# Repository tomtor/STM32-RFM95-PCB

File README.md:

# AVR128DB28
AVR Printed Circuit Board for creating IOT nodes with the RFM95 LORA chip.

See:
- https://www.thethingsnetwork.org/forum/t/avr128db28-pcb-with-rfm95/50864
- https://www.thethingsnetwork.org/labs/story/a-cheap-stm32-arduino-node

for background and old software samples.

This repository now has tested LMIC (https://github.com/tomtor/STM32-RFM95-PCB/tree/master/AVR128DBLora) and RadioLib (https://github.com/tomtor/STM32-RFM95-PCB/tree/master/AVR128_RadioLib) Arduino code for the AVR128DB board with the RFM95W.

Schema: https://github.com/tomtor/STM32-RFM95-PCB/raw/master/AVR-LORA.pdf

Note that most components are optional:

- A LED to flash
- I2C 4K7 pull up resistors
- A lot of capacitors (mounting a single 1uF will do in most situations)
- 32.768kHz crystal
- 24MHz crystal
- MCP1700 regulator with 1uA idle current
- Schottky diode for charging NiMH batteries from a solar panel
- Voltage divider for measuring battery voltage

Aisler link for producing 1206 board: https://aisler.net/p/EAZHDDHF

Aisler link for producing 0805 board: https://aisler.net/p/ZRKAROVP

# STM32-RFM95-PCB
STM32 Printed Circuit Board for creating IOT nodes with the RFM95 LORA chip

See:
- https://www.thethingsnetwork.org/labs/story/a-cheap-stm32-arduino-node
- https://gist.github.com/tomtor/c754355f1b98370e78b4025f236d990e (Arduino sketch)

You can order this board here:

https://aisler.net/p/CZGCIFFH

Credits:

https://github.com/myelin/myelin-kicad-libraries (STM32 module KiCad library)

https://github.com/mysensors-kicad/mysensors_symbols (RFM95 KiCad library)

https://github.com/novirium/ESPilot/blob/master/lib/ESPilot.pretty/RFM95.kicad_mod (RFM95 KiCad footprint)

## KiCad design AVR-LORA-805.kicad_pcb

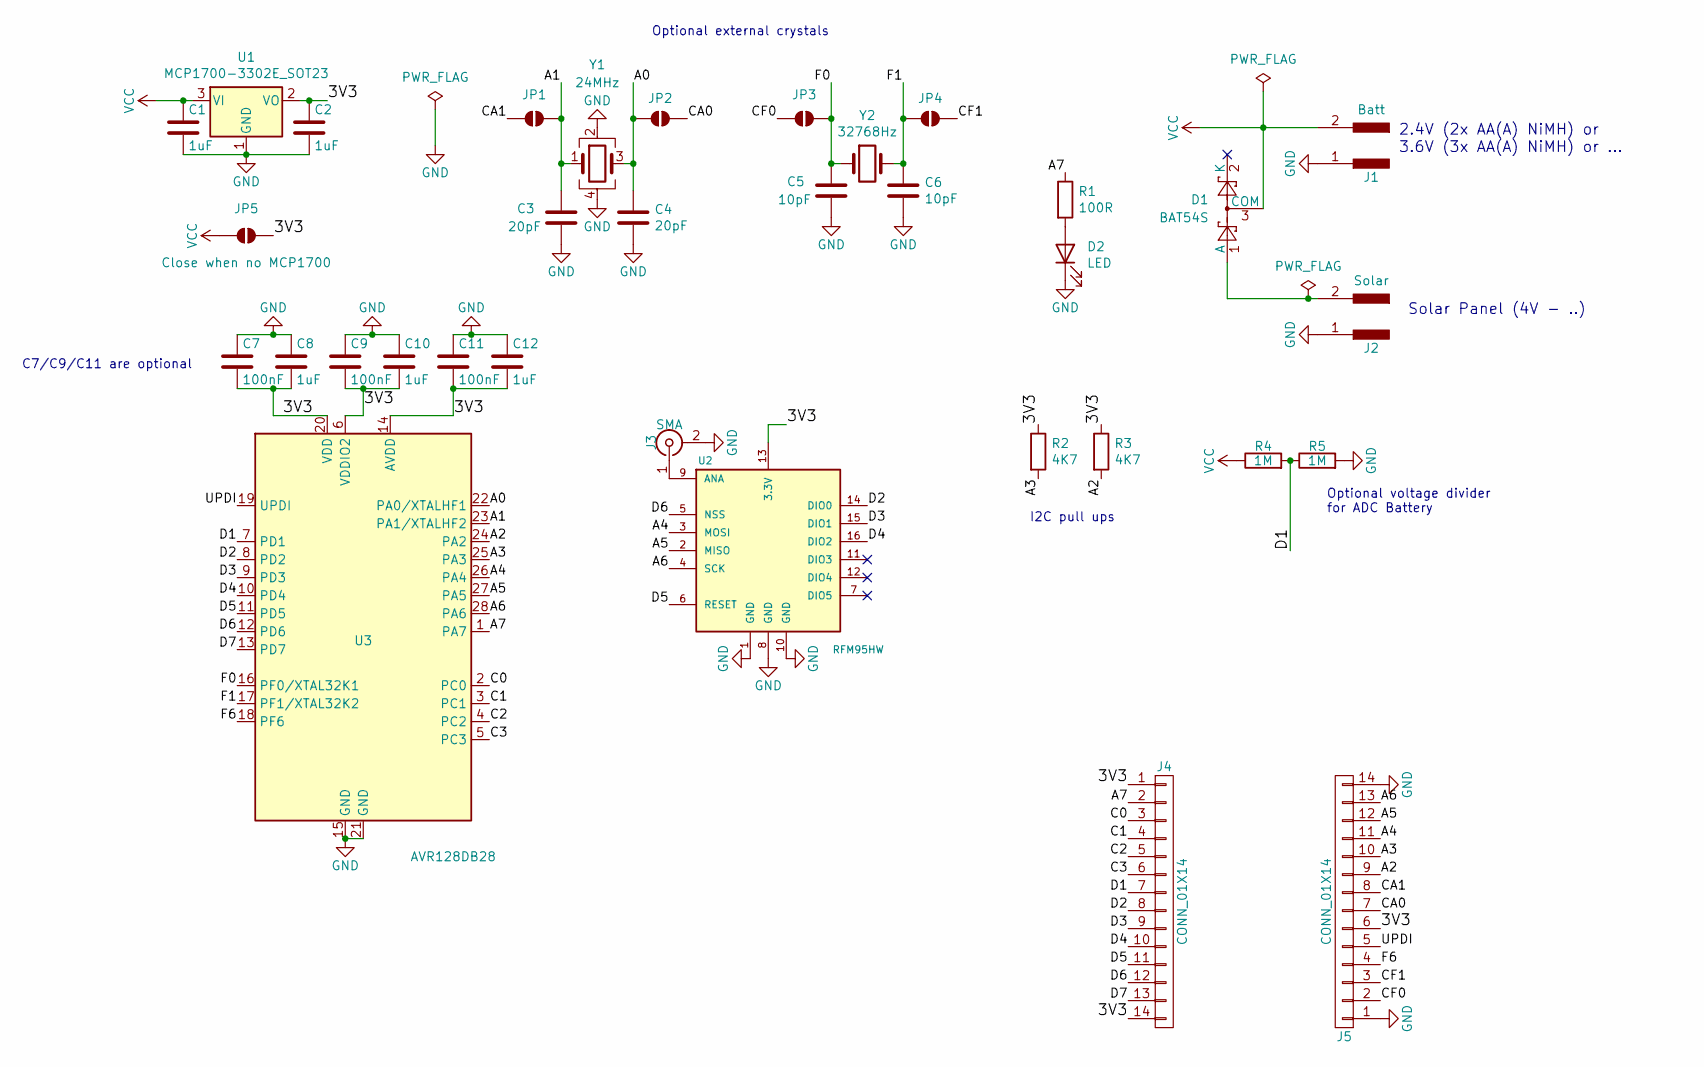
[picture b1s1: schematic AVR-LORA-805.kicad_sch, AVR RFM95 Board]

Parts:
C1, C2, C8, C10, C12: 1uF; C_0805_2012Metric
C3, C4: 20pF; C_0805_2012Metric
C5, C6: 10pF; C_0805_2012Metric
C7, C9, C11: 100nF; C_0805_2012Metric
D1: BAT54S; SOT-23
D2: LED; LED_0805_2012Metric
J1: Batt; PinHeader_1x02_P2.54mm_Vertical
J2: Solar; PinHeader_1x02_P2.54mm_Vertical
J3: SMA; SMA_Amphenol_132134_Vertical
J4, J5: CONN_01X14; PinHeader_1x14_P2.54mm_Vertical
JP1, JP2, JP3, JP4: SolderJumper_2_Open; SolderJumper-2_P1.3mm_Open_Pad1.0x1.5mm
JP5: Close when no MCP1700; SolderJumper-2_P1.3mm_Open_Pad1.0x1.5mm
R1: 100R; R_0805_2012Metric
R2, R3: 4K7; R_0805_2012Metric
R4, R5: 1M; R_0805_2012Metric
U1: MCP1700-3302E_SOT23; SOT-23
U2: RFM95HW; RFM95
U3: AVR128DB28; SOIC-28W_7.5x17.9mm_P1.27mm
Y1: 24MHz; Crystal_SMD_Abracon_ABM8G-4Pin_3.2x2.5mm
Y2: 32768Hz; Crystal_Round_D3.0mm_Vertical

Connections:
/3V3: C2.1, C7.2, C8.2, C9.2, C10.2, C11.2, C12.2, J4.1, J4.14, J5.6, JP5.2 (B), R2.1, R3.1, U1.2 (VO), U2.13 (3.3V), U3.6 (VDDIO2), U3.14 (AVDD), U3.20 (VDD)
/A0: C4.1, JP2.1 (A), U3.22 (PA0/XTALHF1), Y1.3
/A1: C3.1, JP1.1 (A), U3.23 (PA1/XTALHF2), Y1.1
/A2: J5.9, R3.2, U3.24 (PA2)
/A3: J5.10, R2.2, U3.25 (PA3)
/A4: J5.11, U2.3 (MOSI), U3.26 (PA4)
/A5: J5.12, U2.2 (MISO), U3.27 (PA5)
/A6: J5.13, U2.4 (SCK), U3.28 (PA6)
/A7: J4.2, R1.1, U3.1 (PA7)
/C0: J4.3, U3.2 (PC0)
/C1: J4.4, U3.3 (PC1)
/C2: J4.5, U3.4 (PC2)
/C3: J4.6, U3.5 (PC3)
/CA0: J5.7, JP2.2 (B)
/CA1: J5.8, JP1.2 (B)
/CF0: J5.2, JP3.2 (B)
/CF1: J5.3, JP4.2 (B)
/D1: J4.7, R4.2, R5.1, U3.7 (PD1)
/D2: J4.8, U2.14 (DIO0), U3.8 (PD2)
/D3: J4.9, U2.15 (DIO1), U3.9 (PD3)
/D4: J4.10, U2.16 (DIO2), U3.10 (PD4)
/D5: J4.11, U2.6 (RESET), U3.11 (PD5)
/D6: J4.12, U2.5 (NSS), U3.12 (PD6)
/D7: J4.13, U3.13 (PD7)
/F0: C5.1, JP3.1 (A), U3.16 (PF0/XTAL32K1), Y2.1
/F1: C6.1, JP4.1 (A), U3.17 (PF1/XTAL32K2), Y2.2
/F6: J5.4, U3.18 (PF6)
/UPDI: J5.5, U3.19 (UPDI)
GND: C1.2, C2.2, C3.2, C4.2, C5.2, C6.2, C7.1, C8.1, C9.1, C10.1, C11.1, C12.1, D2.1 (K), J1.1, J2.1, J3.2 (Ext), J5.1, J5.14, R5.2, U1.1 (GND), U2.1 (GND), U2.8 (GND), U2.10 (GND), U3.15 (GND), U3.21 (GND), Y1.2, Y1.4
unnamed: D1.1 (A), J2.2
unnamed: D2.2 (A), R1.2
unnamed: J3.1 (In), U2.9 (ANA)
VCC: C1.1, D1.3 (COM), J1.2, JP5.1 (A), R4.1, U1.3 (VI)

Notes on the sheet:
Optional external crystals
Solar Panel (4V - ..)
C7/C9/C11 are optional
I2C pull ups
2.4V (2x AA(A) NiMH) or 3.6V (3x AA(A) NiMH) or ...
Optional voltage divider for ADC Battery

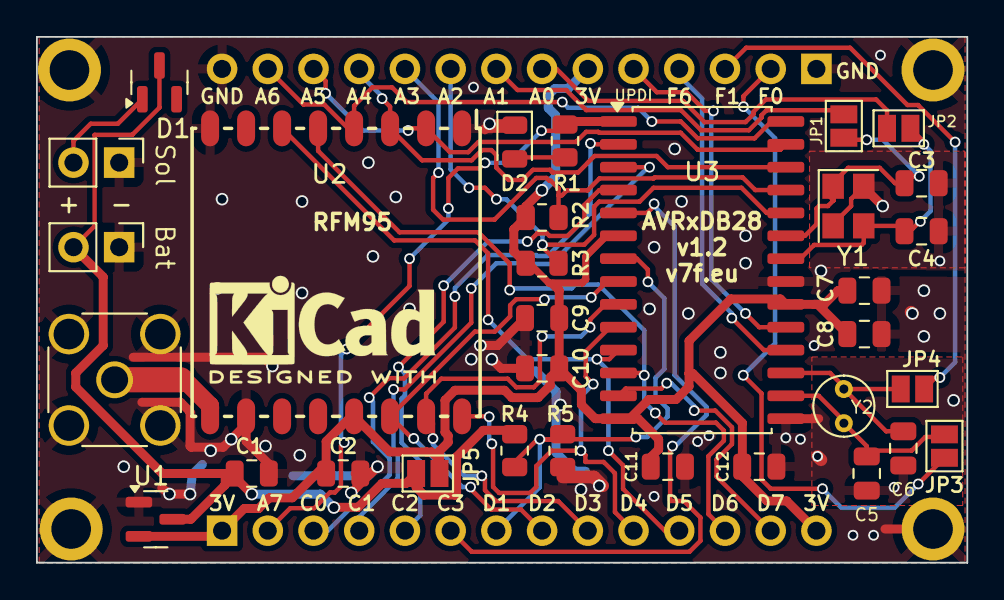
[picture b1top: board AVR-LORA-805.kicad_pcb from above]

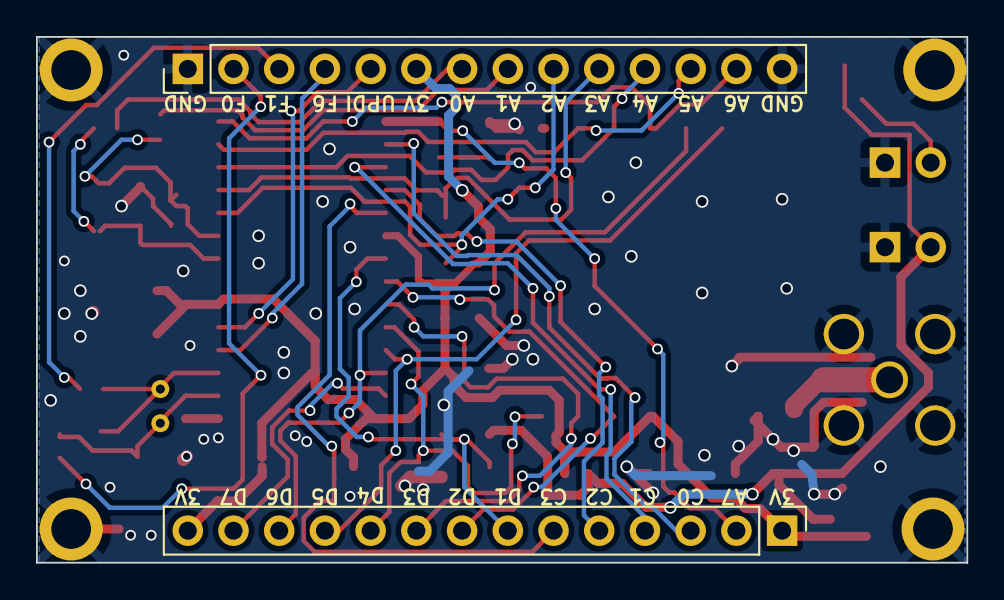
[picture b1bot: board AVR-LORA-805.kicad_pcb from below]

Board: 2 copper layers, 51.7 x 29.2 mm, 34 parts (2 on the bottom side), 33 nets.

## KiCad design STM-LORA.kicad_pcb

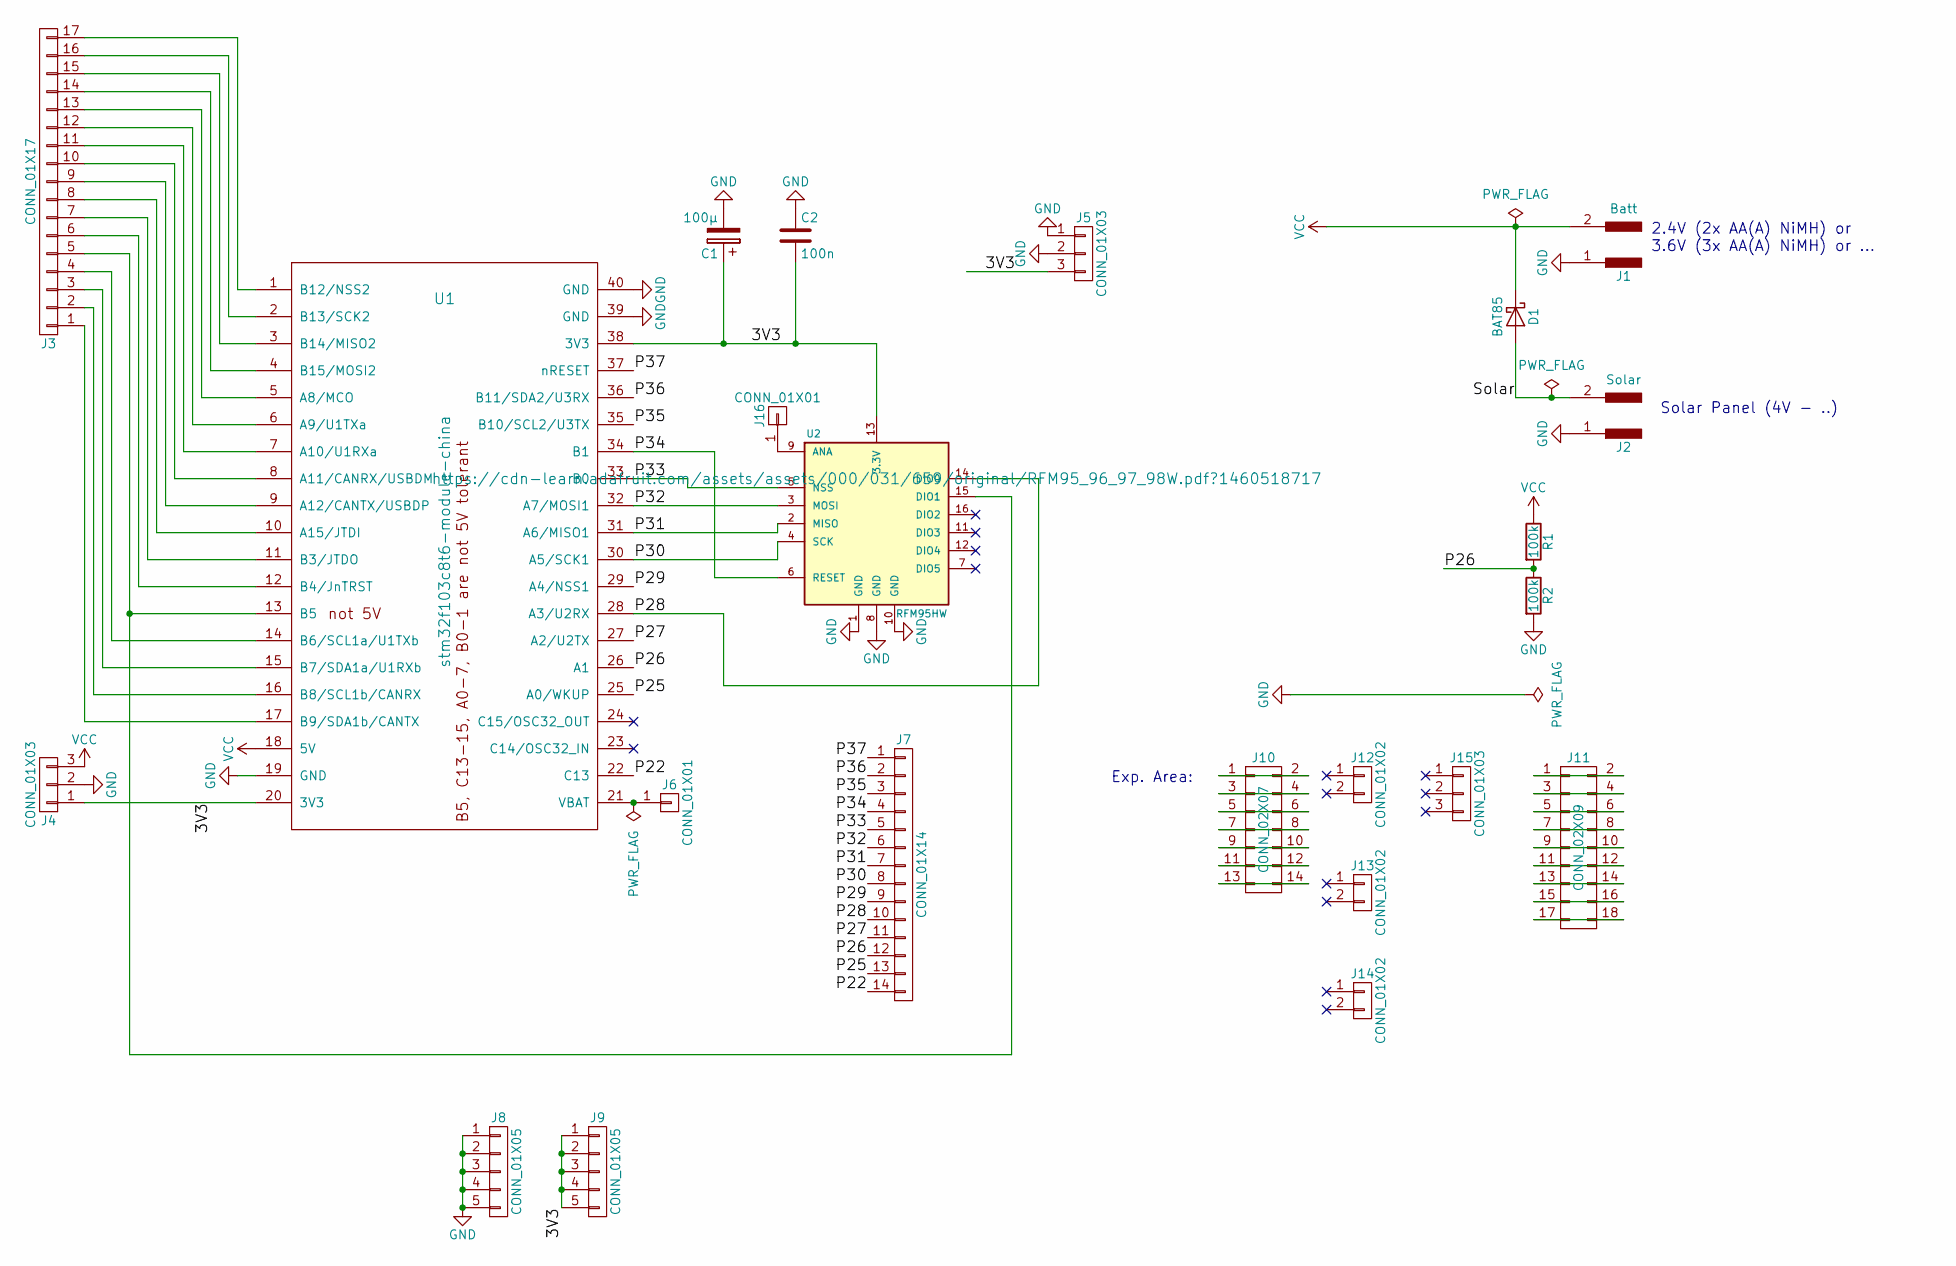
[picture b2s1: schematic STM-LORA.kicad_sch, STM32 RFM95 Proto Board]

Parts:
C1: 100µ; CP_Radial_D6.3mm_P2.50mm
C2: 100n; C_Disc_D5.0mm_W2.5mm_P2.50mm
D1: BAT85; D_DO-35_SOD27_P2.54mm_Vertical_AnodeUp
J1: Batt; PinHeader_1x02_P2.54mm_Vertical
J2: Solar; PinHeader_1x02_P2.54mm_Vertical
J3: CONN_01X17; PinHeader_1x17_P2.54mm_Vertical
J4, J5, J15: CONN_01X03; PinHeader_1x03_P2.54mm_Vertical
J6, J16: CONN_01X01; PinHeader_1x01_P2.54mm_Vertical
J7: CONN_01X14; PinHeader_1x14_P2.54mm_Vertical
J8, J9: CONN_01X05; PinHeader_1x05_P2.54mm_Vertical
J10: CONN_02X07; PinHeader_2x07_P2.54mm_Vertical
J11: CONN_02X09; PinHeader_2x09_P2.54mm_Vertical
J12, J13, J14: CONN_01X02; PinHeader_1x02_P2.54mm_Vertical
R1, R2: 100k; R_Axial_DIN0309_L9.0mm_D3.2mm_P2.54mm_Vertical
U1: stm32f103c8t6-module-china
U2: RFM95HW; RFM95

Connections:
/3V3: C1.1, C2.2, J4.1, J5.3, J9.1, J9.2, J9.3, J9.4, J9.5, U1.20 (3V3), U1.38 (3V3), U2.13 (3.3V)
/P22: J7.14, U1.22 (C13)
/P25: J7.13, U1.25 (A0/WKUP)
/P26: J7.12, R1.2, R2.1, U1.26 (A1)
/P27: J7.11, U1.27 (A2/U2TX)
/P28: J7.10, U1.28 (A3/U2RX), U2.14 (DIO0)
/P29: J7.9, U1.29 (A4/NSS1)
/P30: J7.8, U1.30 (A5/SCK1), U2.4 (SCK)
/P31: J7.7, U1.31 (A6/MISO1), U2.2 (MISO)
/P32: J7.6, U1.32 (A7/MOSI1), U2.3 (MOSI)
/P33: J7.5, U1.33 (B0), U2.5 (NSS)
/P34: J7.4, U1.34 (B1), U2.6 (RESET)
/P35: J7.3, U1.35 (B10/SCL2/U3TX)
/P36: J7.2, U1.36 (B11/SDA2/U3RX)
/P37: J7.1, U1.37 (nRESET)
/Solar: D1.2 (A), J2.2
GND: C1.2, C2.1, J1.1, J2.1, J4.2, J5.1, J5.2, J8.1, J8.2, J8.3, J8.4, J8.5, R2.2, U1.19 (GND), U1.39 (GND), U1.40 (GND), U2.1 (GND), U2.8 (GND), U2.10 (GND)
unnamed: J3.1, U1.17 (B9/SDA1b/CANTX)
unnamed: J3.2, U1.16 (B8/SCL1b/CANRX)
unnamed: J3.3, U1.15 (B7/SDA1a/U1RXb)
unnamed: J3.4, U1.14 (B6/SCL1a/U1TXb)
unnamed: J3.5, U1.13 (B5), U2.15 (DIO1)
unnamed: J3.6, U1.12 (B4/JnTRST)
unnamed: J3.7, U1.11 (B3/JTDO)
unnamed: J3.8, U1.10 (A15/JTDI)
unnamed: J3.9, U1.9 (A12/CANTX/USBDP)
unnamed: J3.10, U1.8 (A11/CANRX/USBDM)
unnamed: J3.11, U1.7 (A10/U1RXa)
unnamed: J3.12, U1.6 (A9/U1TXa)
unnamed: J3.13, U1.5 (A8/MCO)
unnamed: J3.14, U1.4 (B15/MOSI2)
unnamed: J3.15, U1.3 (B14/MISO2)
unnamed: J3.16, U1.2 (B13/SCK2)
unnamed: J3.17, U1.1 (B12/NSS2)
unnamed: J6.1, U1.21 (VBAT)
unnamed: J10.1, J10.2
unnamed: J10.3, J10.4
unnamed: J10.5, J10.6
unnamed: J10.7, J10.8
unnamed: J10.9, J10.10
unnamed: J10.11, J10.12
unnamed: J10.13, J10.14
unnamed: J11.1, J11.2
unnamed: J11.3, J11.4
unnamed: J11.5, J11.6
unnamed: J11.7, J11.8
unnamed: J11.9, J11.10
unnamed: J11.11, J11.12
unnamed: J11.13, J11.14
unnamed: J11.15, J11.16
unnamed: J11.17, J11.18
unnamed: J16.1, U2.9 (ANA)
VCC: D1.1 (K), J1.2, J4.3, R1.1, U1.18 (5V)

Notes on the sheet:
Exp. Area:
2.4V (2x AA(A) NiMH) or 3.6V (3x AA(A) NiMH) or ...
Solar Panel (4V - ..)

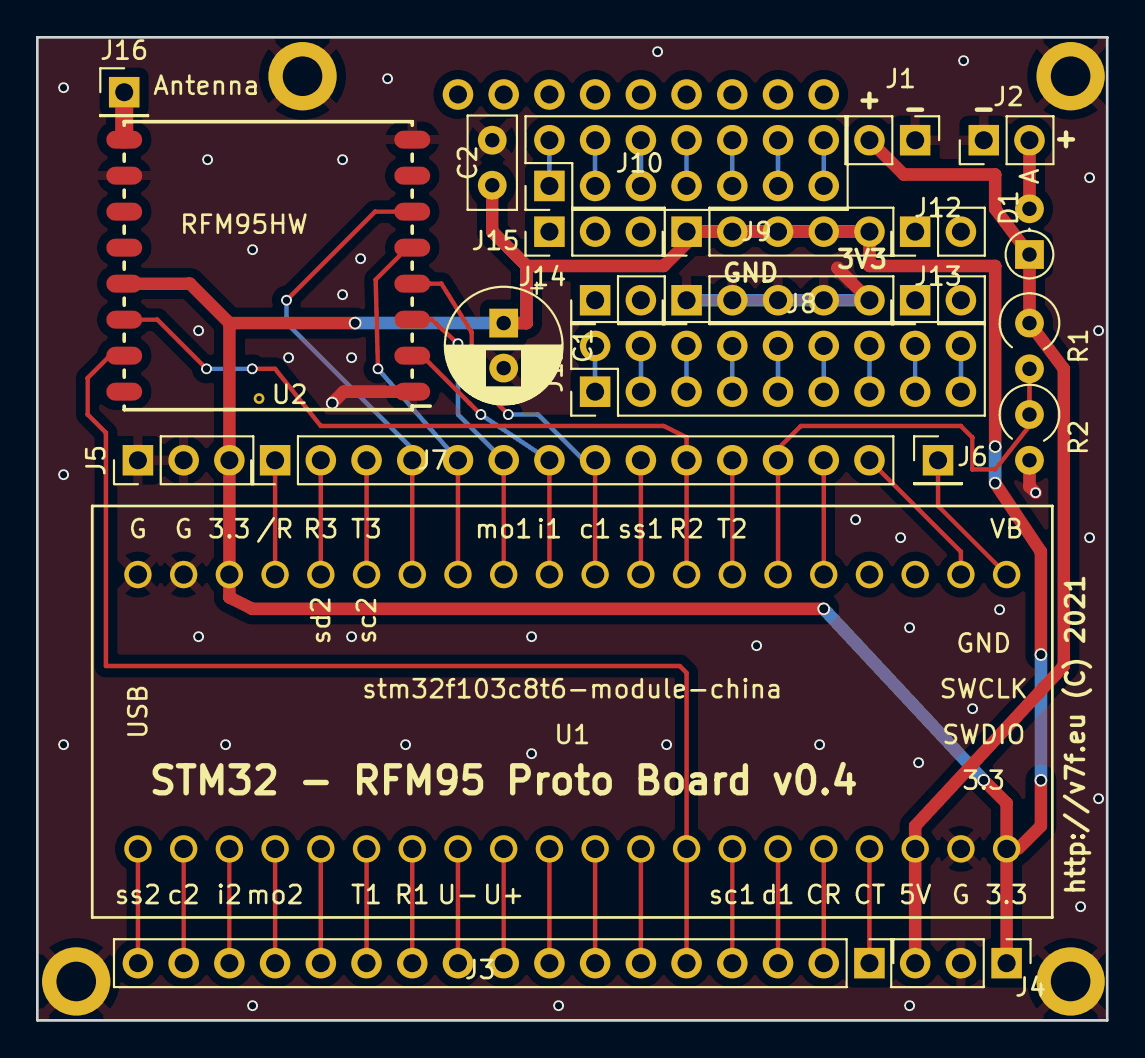
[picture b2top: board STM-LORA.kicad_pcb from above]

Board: 2 copper layers, 59.4 x 54.6 mm, 23 parts (0 on the bottom side), 53 nets.

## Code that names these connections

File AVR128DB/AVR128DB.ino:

#define led       PIN_PA7

#define ON_TIME   4

#define USE_OSC 1

// Slowdown 2 sec every 24 hours:
// 24 * 3600 / 2 = 43200 ticks with 2 second interval in 24 hours.
// Adjustment is in steps of 2 seconds (a tick increments the clock with 2 seconds).

#if USE_OSC
#define ADJUST -(43200/46) // about 100s slow each 24 hrs
#else
#define ADJUST 17200 // About 5s fast in 24hrs
#endif


#include <avr/sleep.h>

void RTC_init(void)
{
  /* Initialize RTC: */
  while (RTC.STATUS > 0)
  {
    ;                                   /* Wait for all register to be synchronized */
  }
#if USE_OSC
  RTC.CLKSEL = RTC_CLKSEL_OSC32K_gc;    /* 32.768kHz Internal Ultra-Low-Power Oscillator (OSCULP32K) */
#else
  _PROTECTED_WRITE(CLKCTRL.XOSC32KCTRLA, 0x3);

  while (RTC.STATUS > 0) ;

  RTC.CLKSEL = RTC_CLKSEL_XOSC32K_gc;   /* 32.768kHz External Oscillator */
#endif

  RTC.PITINTCTRL = RTC_PI_bm;           /* PIT Interrupt: enabled */

  // For 2s overflow ticks while sleeping:
  RTC.INTCTRL = RTC_OVF_bm;
  
  RTC.CTRLA = RTC_PRESCALER_DIV1_gc | RTC_RUNSTDBY_bm | RTC_RTCEN_bm;
}


volatile uint16_t ticks;

ISR(RTC_PIT_vect)
{
  if (ticks)
    ticks--;

  RTC.PITINTFLAGS = RTC_PI_bm;          /* Clear interrupt flag by writing '1' (required) */
}


volatile uint8_t sec2s, hours, minutes; // 2s ticks


ISR(RTC_CNT_vect)
{
  static unsigned int adjust_ticks;
#if ADJUST > 0
  if (++adjust_ticks == ADJUST) {
    adjust_ticks = 0;
  } else {
#elif ADJUST < 0
  if (++adjust_ticks >= -ADJUST && sec2s == 2) { // Do not skip the 0s beat, adjust at 2s beat, skips 4s beat
    adjust_ticks = 0;
    sec2s = 6;
  } else {
#else
  {
#endif
    if (sec2s < 58)
      sec2s += 2;
    else {
      sec2s = 0;
      if (minutes < 59)
        minutes++;
      else {
        minutes = 0;
        if (hours < 23)
          hours++;
        else
          hours = 0;
      }  
    }
  }

  RTC.INTFLAGS = RTC_OVF_bm;          /* Clear interrupt flag by writing '1' (required) */
}


void sleepDelay(uint16_t n)
{
  uint8_t period;
  uint16_t cticks;

  // Before sleeping, disable ADC
  ADC0.CTRLA &= ~ADC_ENABLE_bm; // Very important on the tinyAVR 2-series
  
  if (n < 100) {
      period = RTC_PERIOD_CYC8_gc; // 1/4 ms
      cticks = (n << 1); // Why NOT (n << 2) !?!?!
  } else if (n < 1000) {
      period = RTC_PERIOD_CYC64_gc; // 2 ms
      cticks = (n >> 1);
  } else if (n < 5000) {
      period = RTC_PERIOD_CYC1024_gc; // 32 ms
      cticks = (n >> 5);
  } else {
      period = RTC_PERIOD_CYC8192_gc; // 256 ms
      cticks = (n >> 8);
  }

  while (RTC.PITSTATUS & RTC_CTRLBUSY_bm)  // Wait for new settings to synchronize
    ;

  RTC.PITCTRLA = period | RTC_PITEN_bm;    // Enable PIT counter: enabled

  while (RTC.PITSTATUS & RTC_CTRLBUSY_bm)  // Wait for new settings to synchronize
    ;
  ticks = cticks;
  uint32_t start = millis();

  while (ticks)
    sleep_cpu();
  
  set_millis(start + n);

  RTC.PITCTRLA = 0;    /* Disable PIT counter */

  // upon waking if you plan to use the ADC
  ADC0.CTRLA |= ~ADC_ENABLE_bm;
}

#if 1
unsigned int getBandgap ()
{
  analogReference(INTERNAL1V024);
  return 10 * analogRead(ADC_VDDDIV10);
} // end of getBandgap
#endif

#if 1
unsigned int getBattery ()
{
  unsigned int val = analogRead(PIN_PD1);

  // 3.0v regulator with voltage divider (820k/820k):
  const float Vref = 3000,
              R = 820000,
              Rintern = 100000000, // ATtiny ADC internalresistance
              Rpar = (R * Rintern) / (R + Rintern);
  const unsigned long scale = Vref * (R + Rpar) / Rpar;
  unsigned int results = scale * val / 0x400;

  return results;
} // end of getBattery
#endif


void blinkN(uint8_t n, uint8_t l = led)
{
  for (uint8_t i = 0; i < n; i++) {
    digitalWrite(l, HIGH);
    sleepDelay(ON_TIME);
    digitalWrite(l, LOW);
    sleepDelay(700);
  }
}


void blinkDec(uint8_t d)
{
  blinkN(d / 10);
  sleepDelay(1500);
  blinkN(d % 10);
  sleepDelay(3000);
}

void blinkDec3(uint16_t d)
{
  blinkN(d / 100);
  sleepDelay(1500);
  blinkDec(d % 100);
}


// the setup routine runs once when you press reset:
void setup() {
  RTC_init();                           /* Initialize the RTC timer */
  //set_sleep_mode(SLEEP_MODE_PWR_DOWN);  /* Set sleep mode to POWER DOWN mode */
  set_sleep_mode(SLEEP_MODE_STANDBY);
  sleep_enable();                       /* Enable sleep mode, but not going to sleep yet */

  pinMode(PIN_PA0, INPUT_PULLUP);
  pinMode(PIN_PA1, INPUT_PULLUP);
  pinMode(PIN_PA2, INPUT_PULLUP);
  pinMode(PIN_PA3, INPUT_PULLUP);
  pinMode(PIN_PA4, INPUT_PULLUP);
  pinMode(PIN_PA5, INPUT_PULLUP);
  pinMode(PIN_PA6, INPUT_PULLUP);
  pinMode(PIN_PA7, INPUT_PULLUP);
  
  pinMode(PIN_PD1, INPUT_PULLUP);
  pinMode(PIN_PD2, INPUT_PULLUP);
  pinMode(PIN_PD3, INPUT_PULLUP);
  pinMode(PIN_PD4, INPUT_PULLUP);
  pinMode(PIN_PD5, INPUT_PULLUP);
  pinMode(PIN_PD6, INPUT_PULLUP);
  pinMode(PIN_PD7, INPUT_PULLUP);
  
  pinMode(PIN_PC0, INPUT_PULLUP);
  pinMode(PIN_PC1, INPUT_PULLUP);
  pinMode(PIN_PC2, INPUT_PULLUP);
  pinMode(PIN_PC3, INPUT_PULLUP);
  
  pinMode(PIN_PF0, INPUT_PULLUP);
  pinMode(PIN_PF1, INPUT_PULLUP);
  
  pinMode(led, OUTPUT);

  for (byte i = 0; i < 3; i++) {
    blinkN(1, led);
  }

  sleepDelay(5000);

  getBandgap(); // drop first

//  while (1) {
//    digitalWriteFast(led, (sec2s & 0x2) ? HIGH : LOW);
//  }
}


unsigned voltage;

volatile unsigned cnt;


// the loop routine runs over and over again forever:
void loop() {

  //unsigned int v = voltage = getBattery();
  unsigned int v = voltage = getBandgap();
  blinkDec((v + 50) / 100);
//  blinkDec3((v + 5) / 10);

  blinkDec(minutes);

//  sleepDelay(5000); return;
  while (sec2s != 0) {
    if (sec2s % 10 == 0 && sec2s <= 55) {
      blinkN(1);
      sleepDelay(9000);
    } else
      sleepDelay(100);
  }

}

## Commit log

2017-03-31 Init
2017-04-01 Added power components
2017-04-02 update STM32 lib, add connectors
2017-04-02 start traces
2017-04-02 version 0.1
2017-04-02 Update edges, silk screen
2017-04-02 update PDFs
2017-04-02 0.1 version sent to production
2017-04-03 add produced 0.1 zip
2017-04-03 added drill file
2017-04-03 Change and add exp headers to schema (0.2)
2017-04-03 hide/clear connector labels
2017-04-03 increase power track/via size
2017-04-04 gnd backplane
2017-04-04 Improve GND backplane
2017-04-04 Add NC to exp area
2017-04-04 improve GND plane and double 3V3 track
2017-04-04 reposition capacitor
2017-04-05 clean up files
2017-04-05 remove more files
2017-04-05 remove fp-lib-table and jpg
2017-04-05 rm fp-lib-table
2017-04-06 Layout silk screen
2017-04-07 add front ground plane
2017-04-07 edit front plane and readd fp-lib-table
2017-04-11 reposition labels
2017-05-29 Add pdf for layout, layers and schema
2017-05-31 Add 0.2 zip with Gerber files
2017-06-10 Move edge labels to center
2017-06-10 move edge
2017-06-10 reset grid origin
2017-06-10 Start bigger NG board
2017-06-11 Connect pads (breadboard like)
2017-06-11 increase width antenna track to 0.5mm
2017-06-11 Connect upper breadboard pads
2017-06-11 restore breadboard tracks on bot sides
2017-06-11 Change GND plane and add 3v3 track
2017-06-13 Add 5 mounting holes (2mm)
2017-06-13 Move 3 holes to corner
2017-06-13 bigger antenna hole (1.3mm) and moved mounting holes
2017-06-14 cleanup vias and texts
2017-06-14 Tidy up ground plane
2017-06-15 Move lower left hole away from edge
2017-06-15 Clean F-fab layer
2017-06-27 Move upper holes inwards
2017-09-22 Antenna hole to 1.5mm
2017-09-23 bigger antenna hole pad
2017-09-23 visibility settings
2017-09-23 hide labels
2017-09-23 hide more references
2021-05-02 Version 0.4 Add antenna hole
2021-05-02 Add aisler.net order reference
2021-05-03 Convert libs for Kicad 5.1
2021-08-17 Add AVR128DB28 symbol
2021-08-17 Add AVR schema
2021-08-17 Add AVR connectors
2021-08-17 Add AVR pull ups
2021-08-18 Add AVR crystals
2021-08-18 Add footprints to AVR
2021-08-19 Layout AVR
2021-08-19 Start routing AVR
2021-08-20 Clean DRC AVR
2021-08-21 Cleanup and add pin labels AVR
2021-08-21 Add PDF and PNG to AVR
2021-08-21 Update 32768 config and PDF and PNG for AVR
2021-08-21 Update 24MHz crystal config and PDF and PNG for AVR
2021-08-21 Add AVR info
2021-08-21 Update PDF link
2021-08-21 Add Aisler link
2021-08-21 TTN version
2021-08-21 cleanup back silk screen AVR
2021-08-21 Ground mounting holes AVR
2021-08-22 Better 24Mhz layout AVR
2021-08-22 README
2021-08-22 Add SMA connector
2021-08-22 Update copper fill
2021-08-22 Minor cleanups with labeling
2021-08-22 Ground SMA
2021-08-22 Bigger SMA central pad for soldering wire
2021-08-22 Grow board slightly
2021-08-23 Improve ground plane
2021-08-23 Improve silk screen
2021-08-24 GND SMA connector in schema
2021-08-24 Schema update
2021-08-25 Tune antenne trace to 50 Ohm
2021-08-28 Add 805 AVR variant
2021-08-28 Improve silk 805
2021-08-28 Improve routes 805
2021-09-03 Add KiCAD logo
2021-09-19 Add capacitors to 32768 crystal for 0805 version
2021-09-19 Add capacitors to 32768 crystal for both versions
2021-09-19 1.1 version
2021-09-20 Silk and routing improvements
2021-09-20 crystal grounding
2021-10-06 0805 link and image update
2021-10-17 Demo Arduino sketch
2021-10-17 GND tracks
2021-10-17 GND VIAs
2021-10-21 OSC tuning
2022-01-11 Create LICENSE
2025-02-21 Kicad v9.0.0 version
2025-02-21 Fix warnings on AVR LORA
2025-02-22 Minor cleanups AVR 805 version
2025-02-23 New PDF file
2025-02-23 New AVR LORA PDF
2025-02-23 new schemas and PDFs
2025-02-23 Change battery measure pin
2025-02-24 Update README.md
    Add links to more documentation
2025-02-24 STM-LORA.png
2025-02-24 Update README.md
    Add STM32 LORA board image
2025-02-24 Fix millis() adjustment in sleepDelay()
2025-03-01 Add LORA Sketch example
2025-03-02 Working timing
2025-03-02 LED on when in TX
2025-03-03 add timer mode
2025-03-03 Some cosmetic changes
2025-03-04 send every 15 minutes when nothing counted
2025-03-04 fix no rain timing
2025-03-04 fix more no rain timing
2025-03-05 Use timer TCB in standby instead of idle
2025-03-06 re-add PROGMEM
2025-03-09 Kicad9 STM-Lora schematic
2025-03-10 Add RadioLib example for STM32
2025-03-10 DevId is retrieved from STM32 ROM
2025-03-16 before cleanup
2025-03-16 cleanup
2025-03-16 remove SERIAL_OUT hack
2025-03-19 Add SLEEP_INT, use RTC CMP instead of counting PIT
2025-03-19 Fix order of int enable
2025-03-19 Add .gitignore and compile.sh
2025-03-19 remove wrong nudge
2025-03-20 comment on pending interrupt
2025-03-21 Working version with SLEEPINT
2025-03-21 Add MISO pullip when sleeping
2025-03-21 Remove MISO pullup when sleeping
2025-03-21 Add RadioLib LORA example for AVR128
2025-03-21 Update README.md
    Refer to code samples
2025-03-21 Update README.md
    Links to code
2025-03-23 fix dio1 current leak
2025-03-23 fix dio1 and interrupts
2025-03-23 allow long intervals
2025-03-23 32768 crystal
2025-03-24 enter sleep when waiting for LoraWan reply
2025-03-27 Tested timing
2025-03-30 Add watchdog and optimize division

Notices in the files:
STM-LORA.kicad_pcb:
http://v7f.eu (C) 2021
